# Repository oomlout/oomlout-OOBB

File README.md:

# oomlout-OOBB
OOBB - Open Building Block System

This is the old version.

New version at

https://github.com/oomlout/oomlout_OOBB_V2

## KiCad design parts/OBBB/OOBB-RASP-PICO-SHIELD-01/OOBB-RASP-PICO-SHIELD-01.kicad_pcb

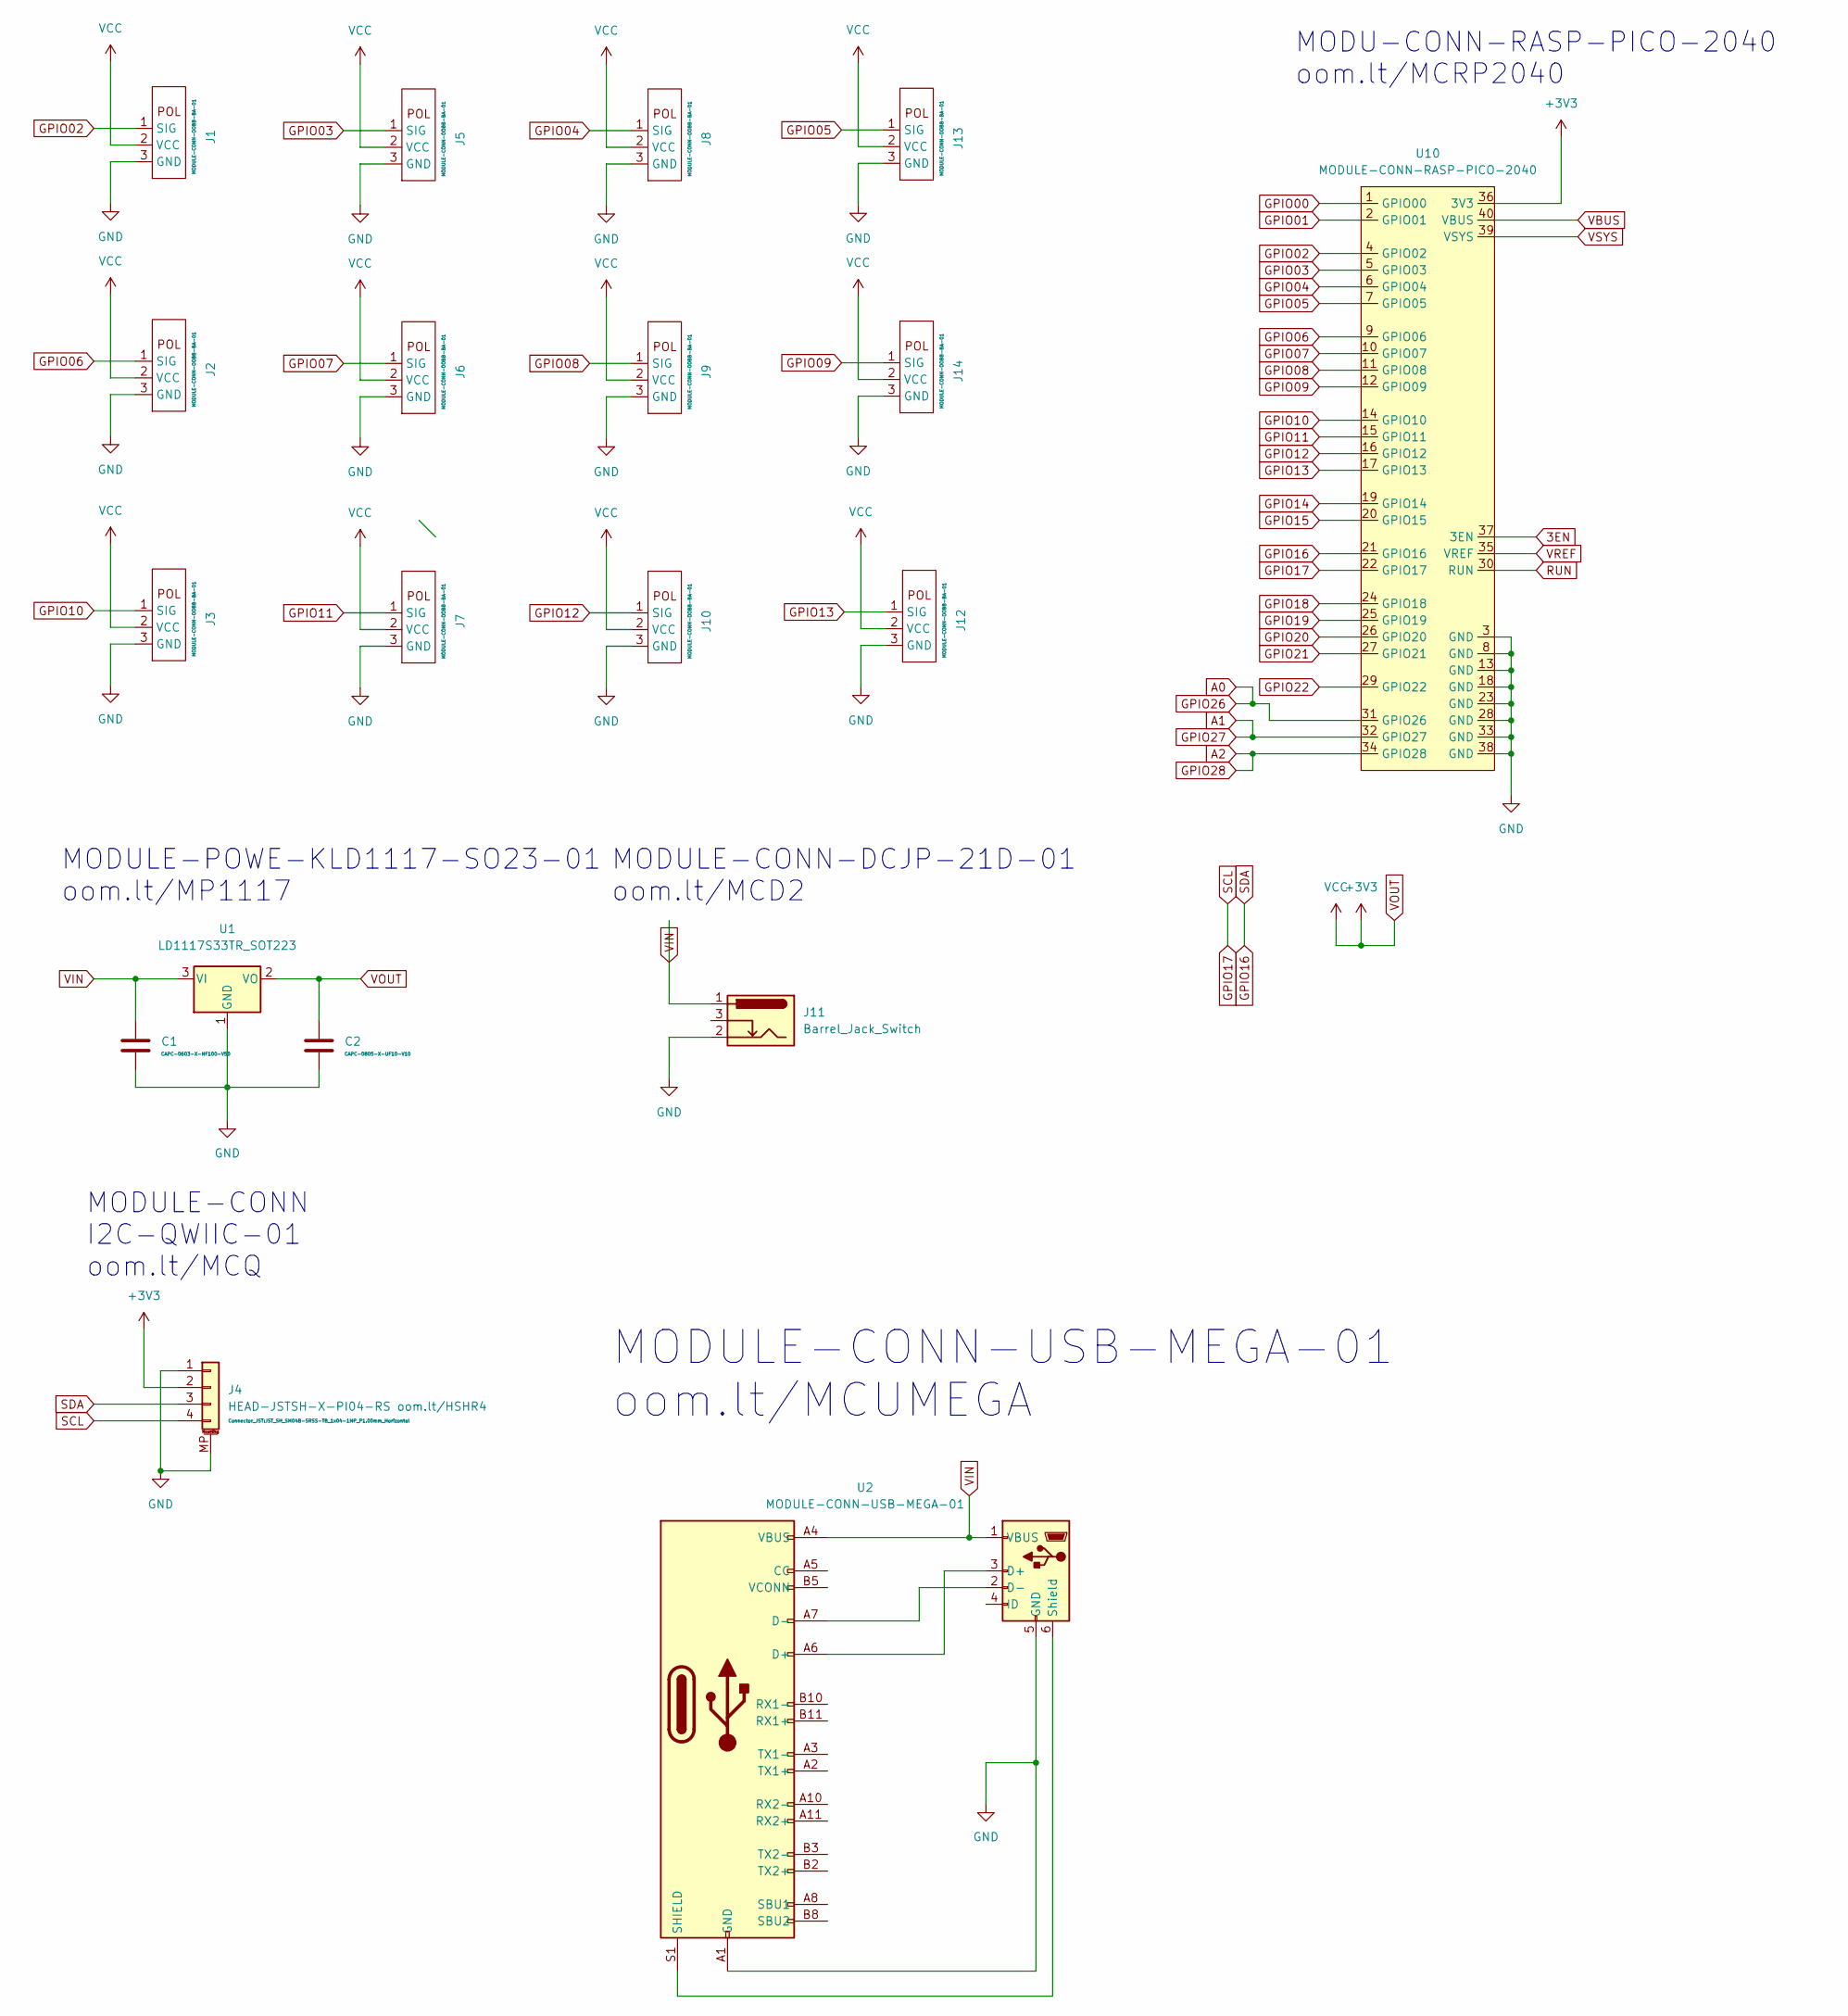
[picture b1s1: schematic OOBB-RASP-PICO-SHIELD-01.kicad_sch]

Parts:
C1: CAPC-0603-X-NF100-V50; C_0603_1608Metric
C2: CAPC-0805-X-UF10-V10; C_0805_2012Metric
J1, J2, J3, J5, J6, J7, J8, J9, J10, J12, J13, J14: MODULE-CONN-OOBB-BA-01
J4: HEAD-JSTSH-X-PI04-RS oom.lt/HSHR4; JST_SH_SM04B-SRSS-TB_1x04-1MP_P1.00mm_Horizontal
J11: Barrel_Jack_Switch; BarrelJack_GCT_DCJ200-10-A_Horizontal
U1: LD1117S33TR_SOT223; SOT-223-3_TabPin2
U2: MODULE-CONN-USB-MEGA-01
U10: MODULE-CONN-RASP-PICO-2040

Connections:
3EN: U10.37 (3EN)
A0: U10.31 (GPIO26)
A1: U10.32 (GPIO27)
A2: U10.34 (GPIO28)
GND: C1.2, C2.2, J1.3 (GND), J2.3 (GND), J3.3 (GND), J4.1, J4.MP (MountPin), J5.3 (GND), J6.3 (GND), J7.3 (GND), J8.3 (GND), J9.3 (GND), J10.3 (GND), J11.2, J12.3 (GND), J13.3 (GND), J14.3 (GND), U1.1 (GND), U2.5 (GND), U2.A1 (GND), U2.A12 (GND), U2.B1 (GND), U2.B12 (GND), U10.3 (GND), U10.8 (GND), U10.13 (GND), U10.18 (GND), U10.23 (GND), U10.28 (GND), U10.33 (GND), U10.38 (GND)
GPIO00: U10.1 (GPIO00)
GPIO01: U10.2 (GPIO01)
GPIO02: J1.1 (SIG), U10.4 (GPIO02)
GPIO03: J5.1 (SIG), U10.5 (GPIO03)
GPIO04: J8.1 (SIG), U10.6 (GPIO04)
GPIO05: J13.1 (SIG), U10.7 (GPIO05)
GPIO06: J2.1 (SIG), U10.9 (GPIO06)
GPIO07: J6.1 (SIG), U10.10 (GPIO07)
GPIO08: J9.1 (SIG), U10.11 (GPIO08)
GPIO09: J14.1 (SIG), U10.12 (GPIO09)
GPIO10: J3.1 (SIG), U10.14 (GPIO10)
GPIO11: J7.1 (SIG), U10.15 (GPIO11)
GPIO12: J10.1 (SIG), U10.16 (GPIO12)
GPIO13: J12.1 (SIG), U10.17 (GPIO13)
GPIO14: U10.19 (GPIO14)
GPIO15: U10.20 (GPIO15)
GPIO16: J4.3, U10.21 (GPIO16)
GPIO17: J4.4, U10.22 (GPIO17)
GPIO18: U10.24 (GPIO18)
GPIO19: U10.25 (GPIO19)
GPIO20: U10.26 (GPIO20)
GPIO21: U10.27 (GPIO21)
GPIO22: U10.29 (GPIO22)
unnamed: U2.2 (D-), U2.A7 (D-)
unnamed: U2.3 (D+), U2.A6 (D+)
unnamed: U2.6 (Shield), U2.S1 (SHIELD)
RUN: U10.30 (RUN)
VBUS: U10.40 (VBUS)
VIN: C1.1, J11.1, U1.3 (VI), U2.1 (VBUS), U2.A4 (VBUS), U2.A9 (VBUS), U2.B4 (VBUS), U2.B9 (VBUS)
VOUT: C2.1, J1.2 (VCC), J2.2 (VCC), J3.2 (VCC), J4.2, J5.2 (VCC), J6.2 (VCC), J7.2 (VCC), J8.2 (VCC), J9.2 (VCC), J10.2 (VCC), J12.2 (VCC), J13.2 (VCC), J14.2 (VCC), U1.2 (VO), U10.36 (3V3)
VREF: U10.35 (VREF)
VSYS: U10.39 (VSYS)

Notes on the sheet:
MODULE-POWE-KLD1117-SO23-01 oom.lt/MP1117
MODULE-CONN I2C-QWIIC-01 oom.lt/MCQ
MODU-CONN-RASP-PICO-2040 oom.lt/MCRP2040
MODULE-CONN-DCJP-21D-01 oom.lt/MCD2
MODULE-CONN-USB-MEGA-01 oom.lt/MCUMEGA

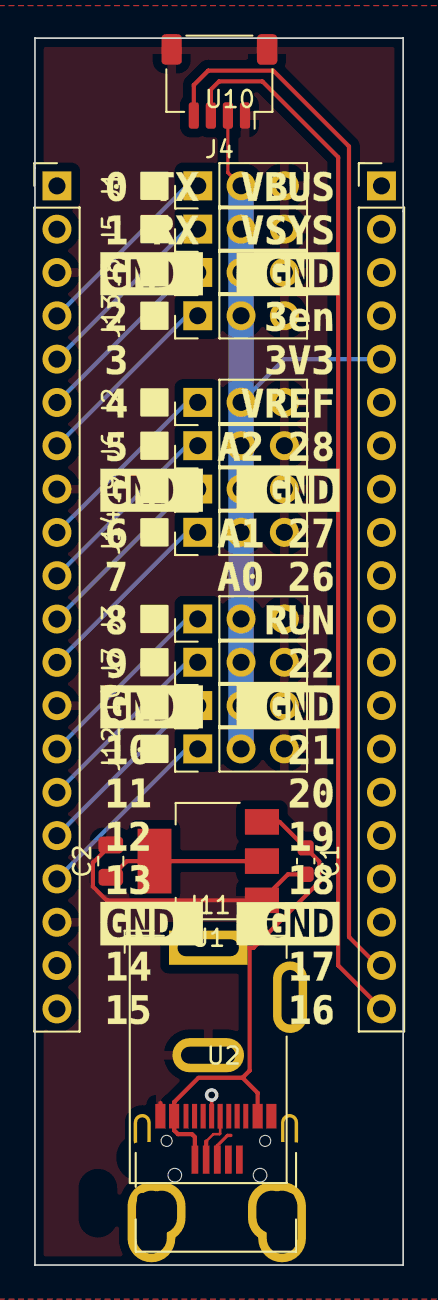
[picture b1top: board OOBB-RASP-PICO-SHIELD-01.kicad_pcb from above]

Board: 2 copper layers, 21.6 x 71.9 mm, 19 parts (0 on the bottom side), 20 nets.

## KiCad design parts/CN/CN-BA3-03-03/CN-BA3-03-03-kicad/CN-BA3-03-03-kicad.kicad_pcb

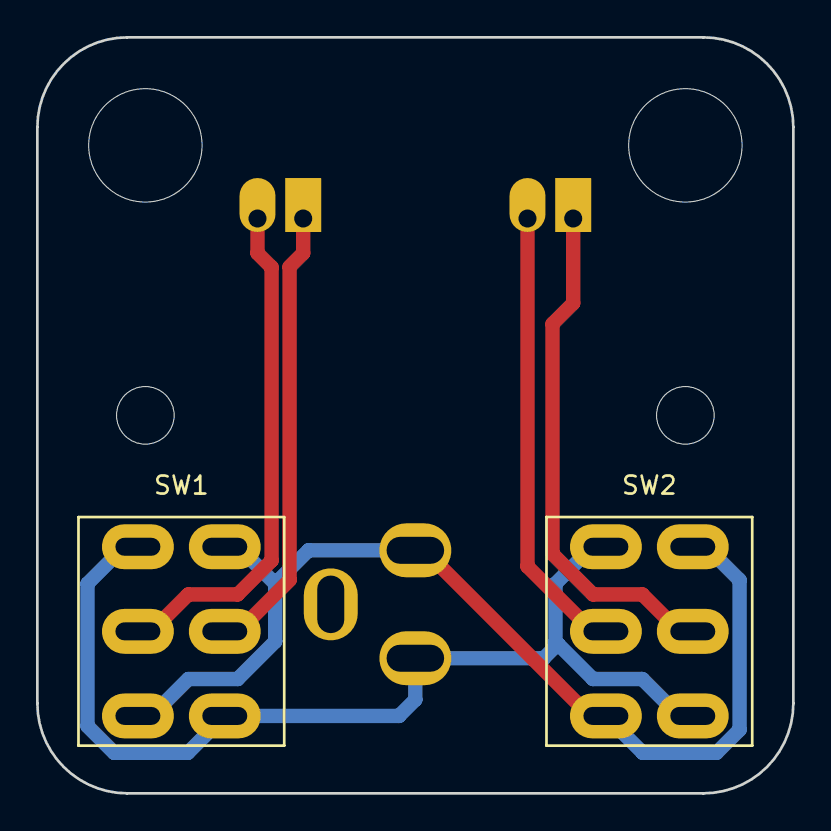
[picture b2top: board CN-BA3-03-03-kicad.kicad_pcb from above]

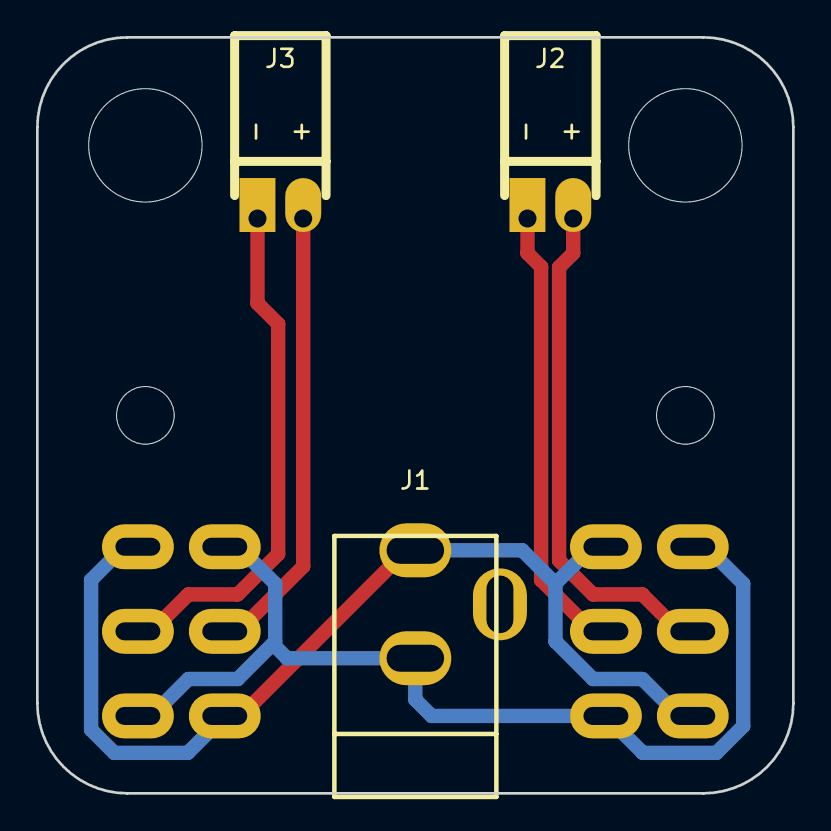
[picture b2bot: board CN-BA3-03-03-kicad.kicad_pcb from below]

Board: 2 copper layers, 42.0 x 42.0 mm, 5 parts (3 on the bottom side), 6 nets.

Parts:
J1: Barrel_Jack_Switch; DCJP-21D-X-THTH-01
J2, J3: Conn_01x02_Male; HEAD-I01-X-PI02-RA-OOBB-WI-M2
SW1, SW2: SW_DPDT_x2; SWIS-50DIX45DI-X-DPDTM-PM

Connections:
+5V: J1.1, SW1.1, SW1.6, SW2.1, SW2.6
GND: J1.2, SW1.3, SW1.4, SW2.3, SW2.4
unnamed: J2.1, SW1.5
unnamed: J2.2, SW1.2
unnamed: J3.1, SW2.5
unnamed: J3.2, SW2.2

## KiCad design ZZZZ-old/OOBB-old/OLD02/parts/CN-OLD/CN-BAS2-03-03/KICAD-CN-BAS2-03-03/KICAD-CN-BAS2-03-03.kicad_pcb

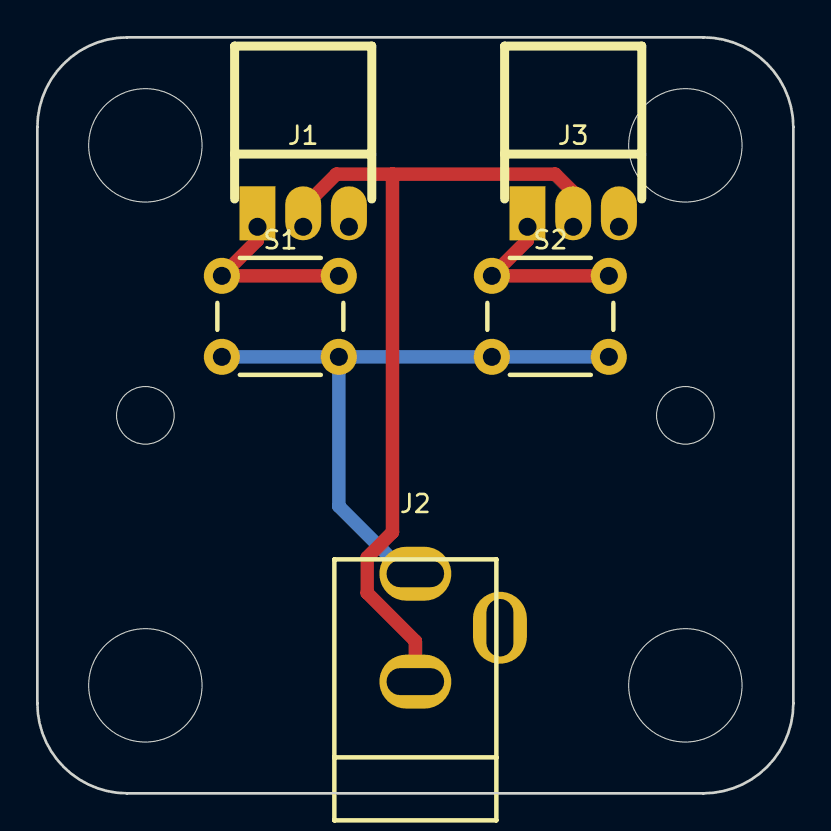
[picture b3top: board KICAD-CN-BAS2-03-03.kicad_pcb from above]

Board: 2 copper layers, 42.0 x 42.0 mm, 5 parts (0 on the bottom side), 4 nets.

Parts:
J1, J3: HEAD-I01-X-PI02-01; OOMP-HEAD-I01-X-03PI-RA-ES
J2: DCJP-21D-X-THTH-01; OOMP-DCJP-21D-X-THTH-01
S1, S2: BUTA-06-X-STAN-01; OOMP-BUTA-06-X-STAN-01

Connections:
unnamed: J1.1, S1.1
unnamed: J1.2, J2.2, J3.2
unnamed: J2.1, S1.2, S2.2
unnamed: J3.1, S2.1

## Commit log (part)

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2017-02-17 Added holder for TM1637 controlled 7 segment display.
2017-02-17 Updated HL-JOYS (joystick holder).
2017-02-19 Slight wiki changes.
2017-02-19 Removed nested folder.
2017-02-19 Generated items.
2017-02-23 Generated resolutions and formats for all parts.
2017-02-23 Fixed some typos.
2017-02-23 Fixing up.
2017-02-23 Added details to timing pulley xml files.
2017-02-23 Fixed alphabatrizaion.
2017-02-27 Added a few diagrams.
2017-03-10 Added a HV wiring diagram.
2017-03-10 Added HL-LE3W 5x5 holder.
2017-03-10 Fixed up a couple of WI plates.
2017-03-10 Fixed opening for header poking through, and moved labels for a BA2 rather than stacked BAW.
2017-03-27 Worked on sheets.
2017-03-29 Fixed a double shape.
2018-01-28 Updated servo holder.
2018-01-28 Began adding PT (Plate (Toothed))
2018-10-11 Slight update to PL-04-04.
2018-10-11 Removed the HL category to OOEB
2019-02-07 Added 07-03 and 07-05 plates.
2019-02-15 Added PL-09-03
2019-02-26 Added servo holders back from OOEB.
2019-02-26 Changed the stack from 2 c's to 2 b's.
2019-03-01 Added OOBB-CI-21
2019-03-01 Started adding 3d Models of PL pieces.
2019-03-23 Made a 3d GE-03
2019-03-23 Worked on 3D printed JA
2019-03-23 Worked on a new NEMA 17 motor mount.
2019-03-23 Rotated NEMA17 Motor 15 degrees for clearance.
2019-03-23 Worked on 3d printed jacks.
2019-03-24 New iteration of JA-03-01.
2019-03-24 Laser cutable MM-N17-03-03 stack.
2019-03-25 Worked on 3d Printed jack (made it shorter, see if it 3d prints okay check)
2019-04-02 Worked on 3d printed JA 03-01
2019-04-02 Worked on JA-03-01
2019-04-04 Added a 90 degree captive nut to MM-N17-03-03
2019-04-06 Worked on embeded nuts
2019-04-07 Fixed spacing issue on JA-03-01 in working.
2019-04-07 Added a PL-05-03-30H (for motor mounting help)
2019-04-07 Added a laser cuttable configuration for MM-N17-03-03
2019-04-12 New JA-03-01 Approach
2019-04-21 Added MM-N17-03-03
2019-04-22 Added JA-03-01 properly
2019-04-22 Updated dimensions.
2019-04-26 Working on jack.
2019-05-08 Worked on more mm-03-03 formats.
2019-05-08 Updated JA-03-01 to new style.
2019-06-01 Working on motor mount.
2019-07-08 Random working.
2019-07-25 Prototyping BP-606-04-01.
2019-07-28 Worked on scaling for 3d printed version.
2019-07-31 Added newly generated PL's.
2019-07-31 Started generating resolutions.
2019-08-01 Partially generated resolutions.
2019-08-02 Partially generated diagrams.
2019-08-02 Working on BP size tests
2019-08-03 Worked on clearances for bearing plates.
2019-08-04 Finished generating resolutions.
2019-08-14 Generated PL sketchup models.
2019-09-03 Generated .obj files for PL plates and worked on JA-03-01
2019-09-03 A few changes.
2019-10-20 Worked on HL-LCD.
2019-10-27 Working on various 3d printing items.
2019-10-27 Split HL-04-01 into it's own directory.
2019-10-28 Fixed M3 screw clearance size in 3D model 3-3.2.
2019-11-15 Working on a bunch of things.
2019-11-15 Moved everything to old to start resizing to 15mm spacing.
2019-11-15 Generated PL's.
2019-11-15 Removed .gitignore oarts/ directory.
2019-11-15 Added JA generation and Test Panel.
2019-11-16 Added markdown pages.
2019-11-16 Up to date generation.
2019-11-17 Changed hole clearance for M6 bolts.
2019-11-17 Regenerated everything.
2019-11-17 Testing wiki.
2019-11-19 Added a union to makeJA's one piece.
2019-11-24 Generated everything.
2019-11-25 Added BP-606-03-03
2019-11-25 Fixed up BP-606-03-03
2019-11-26 Rejigged HL-N17-05-03.
2019-11-27 Fixed up HL-N17-05-03
2019-11-28 Worked on HL-SM-04-03 prototype.
2019-11-28 Added notes to bat files.
2019-11-28 Added more JA sizes.
2019-12-04 Fixed up everything.
2019-12-04 Worked on servo holder.
2019-12-09 Worked on a few pieces.
2019-12-12 Worked on HL-SM
2019-12-12 Getting everything ready to generate.
2019-12-14 Changed thickness of BP to 12 mm to match jacks.
2019-12-14 Added colorscheme to render command.
2019-12-14 Worked on wheels.
2019-12-14 Worked on HL-SM-03-03
2019-12-16 Complete regeneration.
2019-12-16 New wheel style.
2019-12-16 Fixed thickness of wheels and bearing plates to 9mm.
2019-12-16 Working on BP-6810-05-05.
2019-12-17 Worked on holders.
2019-12-17 Added PL-01-01
2019-12-17 Worked on servo.
2019-12-17 Worked on CI-03-CA-FL and added keyway to HL-N17-05-05
2019-12-17 Redid wheel style.
2020-01-02 Worked on clearances of JA's.
2020-01-02 Worked on JA's
2020-01-03 worked on HL-SM.
2020-01-03 changed clearance on servo horn.
2020-01-03 Added a servo horn hole tester.
2020-01-03 Added new pause heights for HL-SM horn
2020-01-03 Did a revision on HL-SM-03-03 fixing a few things.
2020-01-04 Worked on the servo horn.
2020-01-04 added a comment
2020-01-04 Worked on servo horn a bit.
2020-01-04 Added Bearing6704 test piece.
2020-01-04 Cosmetic changes.
2020-01-04 Getting Ready to regenerate.
2020-01-05 Regenerated HL-SM.-03-03 new bearing hold size
2020-01-05 Added a twist to CI-03 and WH-03
2020-01-05 Fixed a bearing size error.
2020-01-06 Changed wheels from double bearing to single embedded.
2020-01-06 Added WH pause height note.
2020-01-06 Changed M3 Countersink top size.
2020-01-06 Worked on a few test pieces.
2020-01-06 Fixed position of servo horn cutout.
2020-01-07 Added pi zero holder.
2020-01-07 A few cosmetic changes on HL-SM-03-03
2020-01-07 Regenerated models.
2020-01-07 Fized rivet size in HL-PZ-05-03
2020-01-07 Generated HL-PZ-05-03
2020-01-07 Rotated Pi Zero placement on holder.
2020-01-07 Fixed some spacing issues with HL-SM-03-03.
2020-01-15 Worked on HL-SM-03-03.
2020-01-16 Finished complete generation.
2020-01-17 Added nut sizes.
2020-01-17 Testing different bearing sizes.
2020-01-17 Added pi camera holder.
2020-01-17 Added single sided servo horn test.
2020-01-17 Single sided servo horn in horn.
2020-01-17 Fixed Pi Camera Mount.
2020-01-17 Updated HL-SM-03-03
2020-01-18 Worked on camera holder.
2020-01-18 Regenerated HL-SM-03-03
2020-01-20 A few HL-SM-03-03 nudges
2020-01-21 Worked on battery holder.
2020-01-21 Fixed op CP.
2020-01-24 Worked on things a bit.
2020-01-25 Added first layer lip to wheels.
2020-01-25 Made hole for servo bigger.
2020-01-31 Tweaked HL-SM-03-03 for silly mistakes.
2020-01-31 Wheels with proper servo horn adapter.
2020-01-31 A few minor tidies.
2020-02-01 Fixed bolt spacing on bracket.
2020-02-02 Split HL-SM-03-03 generation to new file.
2020-02-03 Made 3DPR generate first.
2020-02-04 Changed servo height.
2020-02-04 Relatively cemented HL-SM-03-03
2020-02-05 Fixed JA's
2020-02-07 Worked on servo horn with captured bearing.
2020-02-08 Working on HL-SM-03-03
2020-02-09 Regenerated all.
2020-02-10 Worked on bearing tests.
2020-02-10 Short notes.
2020-03-04 Worked on new servo horn.
2020-03-04 Worked on holder part for new style.
2020-03-04 Worked on BP-6810-05-05
2020-03-04 Worked on BP-6806-04-04
2020-03-05 Fixed bearing old sizes.
2020-03-05 Worked on bearing blocks.
2020-03-06 Worked on bearing plates.
2020-03-07 Worked on BP-6810-05-05 fixed bearing clearance.
2020-03-10 Improved spin of HL-SM-03-03
2020-05-01 fixed holes not appearing in 2d PL's
2020-05-02 Regenerated all plates wheels and circles (fix missing circles in 2d version)
2020-05-02 fixed 2d versions.
2020-05-07 Worked on HL-SE a bit.
2020-05-07 Worked on SE bracket.
2020-05-08 Worked on servo holders.
2020-05-09 Worked on B1X
2020-05-09 Worked on HL-SE-05-03 servo spacing.
2020-05-10 Fixed battery and USB location on B1X.
2020-05-10 fixed height of base.
2020-05-16 Worked on OBBB
2020-05-17 Added plug to B1X
2020-05-17 Working on clearances for OOEB connector printing.
2020-05-19 Figured out clearance for OOEB (default 0.5)
2020-06-02 Working on OBBB.
2020-06-25 Refactoring HL-SE generation. (Broken)
2020-06-27 Refactoring.
2020-06-28 Worked on rationalized code and HL-SE-05.
2020-06-29 Fixed HOLDERB height.
2020-06-29 Fixed screw height.
2020-07-18 Made servohord defult to 03-01 rather tan wheel.
2020-07-21 All updated.
2020-07-22 Working on servo holder.
2020-07-27 Iterating on HL-SE-05-03
2020-08-31 Added parts for 1908 Mechano catalogue.
2020-08-31 Finished generating.
2020-09-01 Testing thickness on PL-01's
2020-09-02 Added PL-11-01 thicknesses.
2021-07-11 Added OPSC calls to OOBB (ultimately transitioning to this)
2021-07-12 Generated gearmotor holders.
2021-07-13 Added tripod holder.
2021-07-13 A new attempt at GM1
2021-07-13 Regenerated gearnmotor holders.
2021-07-13 Worked on CN-BAS2 initial.
2021-07-14 Added OOEBWIMOT Test piece.
2021-07-15 Worked on CN's
2021-07-17 Worked on GM1 Shaft test piece.
2021-07-18 Worked on GM1 Test.
2021-07-18 Fixed an error.
2021-07-19 Added wire path and counter sink to HL-GM1.
2021-07-19 Testing out GM1 shaft changes.
2021-07-19 Worked on HL-GM1.
2021-08-01 Worked on wiring options.
2021-08-02 Refined HL-GM1.
2021-08-02 Added extra baseplate styles.
2021-08-02 Worked on a few things.
2021-08-02 A few more changes.
2021-08-02 Got mounting holes for RC bits in.
2021-08-04 Fixed WH-GM1 Clearance.
2021-08-06 Worked on CN-BA3 and added reference and kicad footprints.
2021-08-09 R
    Removed generic BP (replaced with different types)
2021-08-09 Made WI gen full again.
2021-08-17 Worked on WI's
2021-08-17 Worked on a N20 shaft test card.
2021-08-17 New clearances for N20 shaft test card.
2021-08-24 Worked on N20
2021-08-28 A few new things and a few fixes.
2021-08-28 Gearmotor adapter PCB.
2021-08-29 Added clearance for DCJP solder lugs
2021-08-30 Worked on shaft for new GM1 shaft size.
2021-08-31 HL-GM1 and WH-03-GM1 working.
2021-08-31 Worked on WH-03-GM1 and HL-GM1
2021-09-01 Fixed up countersunk heights.
2021-09-02 Added OOBB.py to get into OOMP stuff.
2021-09-02 Worked on WH-03-GM1 shaft (added chamfer), changed the way pieces are called.
2021-09-03 Wheel and HL-GM1 work.
2021-09-04 MOved GMOT01 variables to OOBBgv().
2021-09-04 Fixed a batch file callstyle.
2021-09-04 Fixed a few clearances.
2021-09-05 Full regen and deprecation.
2021-09-05 Fixed HL-GM1 thickness.
2021-09-09 Transfer not working.
2021-09-09 Worked on bearing block addition to HL-GM1
2021-09-09 Working on BP6803 GM1 stuff, including wheel rethink.
2021-09-11 Added some shaft spacers.
2021-09-11 Added capscrews.
2021-09-11 Changed WH BP6803 to better fit a bearing.
2021-09-11 Generated HL-GM1-BP6803
2021-09-12 GM1 Working.
2021-09-13 Refactored CI and PL, got rid of old files.
2021-09-13 Added 2D projections to generation, redid circles and most plates to include them.
2021-09-14 Working on HL-GM1 and CI-GM1.
2021-09-15 Workings.
2021-09-15 Added a gear link piece for securing to a shaft.
2021-09-15 Looked at adding extra clearance to HL-GM1
2021-09-16 A lot of little tweaks.
2021-09-20 HL-GM1 Refining.
2021-09-20 Changed gear angle to 20.
2021-09-20 Transfer.
2021-09-21 Worked on HL-GM1 and WH+
2021-09-21 Nut location experimenting.
2021-09-27 Working on inset for 3d printing
2021-09-27 Working away on things.
2021-09-28 Random workings.
2021-09-28 Removed countersinks from HL-GM1-BP6803.
2021-09-29 Realigning.
2021-09-29 Jack Working.
2021-09-29 PL Generation
2021-09-29 BP Full Generation.
2021-09-30 Regenerated all PL's
2021-09-30 Added bearing lip to WH-03-GM1
2021-09-30 Did some jack spacing.
2021-10-02 Added inset to WI's
2021-10-02 Working on GM1 shaft grabber
2021-10-02 Working on GM1 shaft grabber.
2021-10-02 WI Regen and fixup.
2021-10-02 WH fiddling.
2021-10-04 Worked on B4AA battery holder.
2021-10-04 Redid printing side for HL-GM1 BP6803
2021-11-02 Removed CN type.
2021-11-28 Added a caster test.
2021-11-30 Fixed clearance on Controller holder (HL-CN)
2021-11-30 First try at Pi Zero holder (HL-PZ-05-03), and working on BP-606-03-03.
2021-11-30 Added the generated version.
2021-12-04 HL-P4 attempt one.
2022-02-14 Worked on HL-PZ
2022-02-15 Worked on HL-PZ Relatively stable (T3 Test)
2022-02-21 Some BP Work. Regenerated PL's
2022-09-14 Generated all PL's
2022-09-16 OOBB Complete gen and current state.
2022-09-16 Partial BP-6810-05-05 Regen (tighter tolerances.
2022-09-16 Full BP-6810-05-05 Regen.
2022-09-17 Full generation maybe.
2022-09-17 More updates.
2022-09-17 Upgrades.
2022-09-18 Testing changes.
2022-09-22 Working on two sided JAs
2022-09-24 Ja Working.
2022-09-26 HL-SM first works.
2022-10-01 Fixed hole diameters.
2022-10-06 A bit of working.
2022-10-13 Working on PICO shield
